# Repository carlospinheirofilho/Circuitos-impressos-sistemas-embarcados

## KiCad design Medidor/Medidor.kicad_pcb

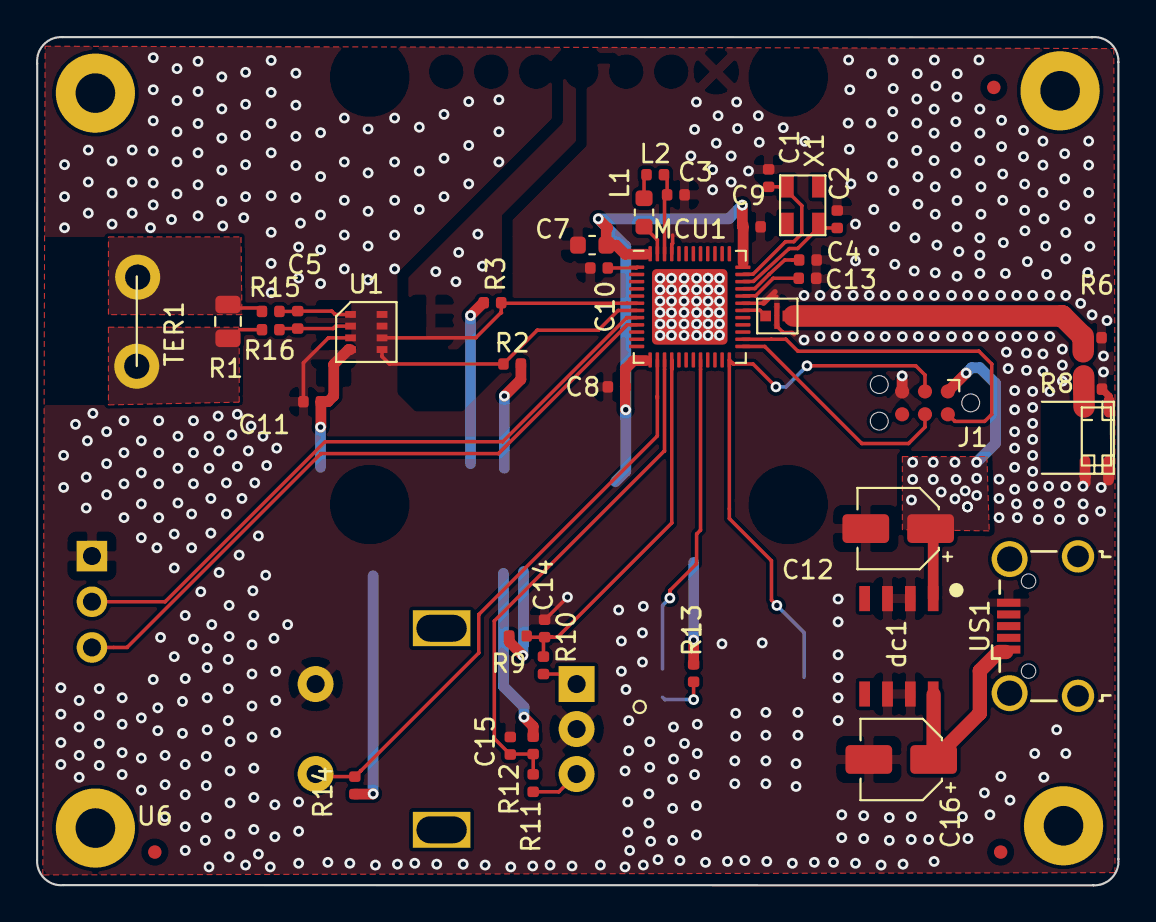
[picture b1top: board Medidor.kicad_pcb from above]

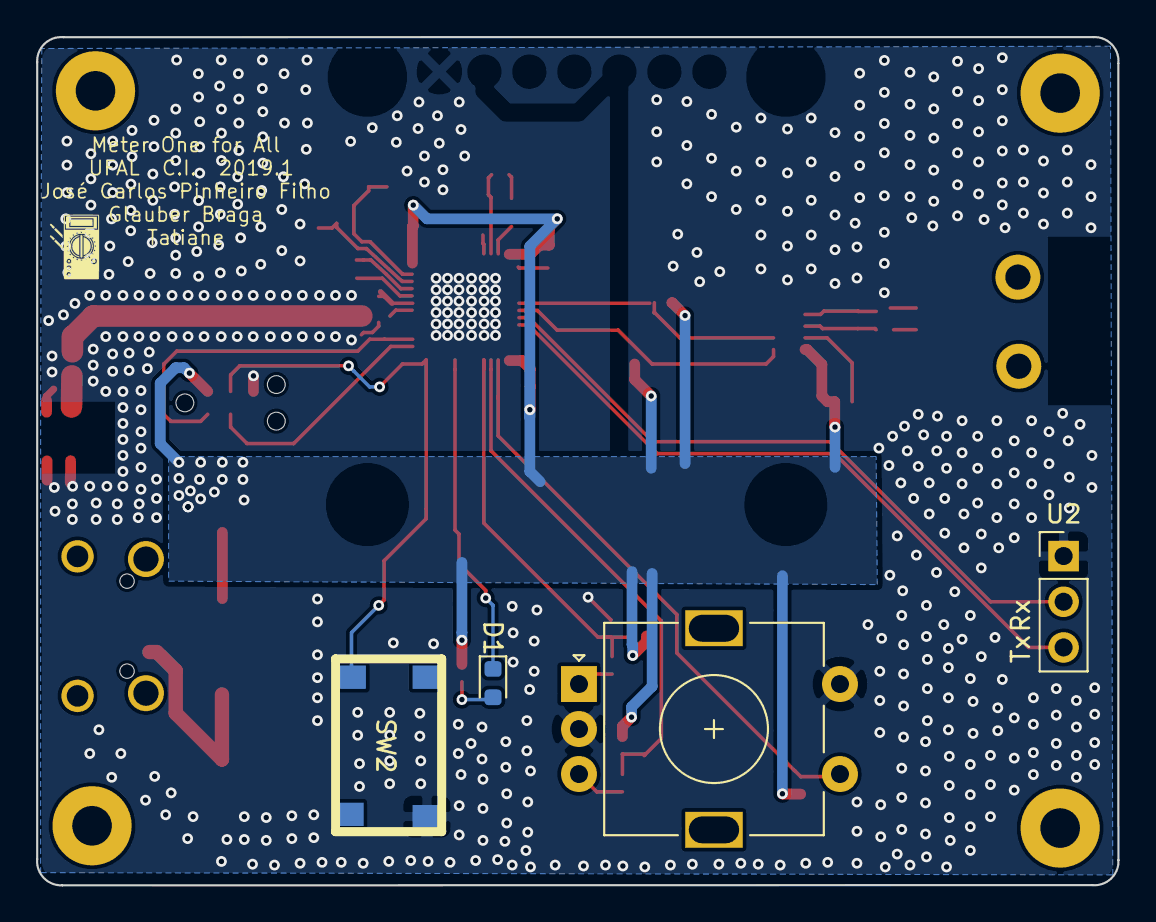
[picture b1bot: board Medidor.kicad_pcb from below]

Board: 2 copper layers, 60.1 x 47.1 mm, 47 parts (4 on the bottom side), 32 nets.

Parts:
C1, C2: 12pF; C_0402_1005Metric
C3: 1uF; C_0402_1005Metric
C4: 100pF; C_0402_1005Metric
C5, C11, C14, C15: 0.1uF; C_0402_1005Metric
C7: 4.7uF; C_0603_1608Metric
C8, C9, C10: 100nF; C_0402_1005Metric
C12: 0.1uF; CP_Elec_4x3
C13: NC; C_0402_1005Metric
C16: 0.33uF; CP_Elec_4x3
D1: LED; LED_0603_1608Metric
Fil1: 2450FM07A0029T; baloon
J1: TC2030-CTX-TAG_CONECT; Tag-Connect_TC2030-IDC-NL_2x03_P1.27mm_Vertical
L1: 10uH; L_0603_1608Metric
L2: 15nH; L_0402_1005Metric
MCU1: nRF52832-QFN4; QFN-48-1EP_6x6mm_P0.4mm_EP4.2x4.2mm
R1: Shunt; R_0805_2012Metric
R2, R3: 1kΩ; R_0402_1005Metric
R6, R8: NC; R_0402_1005Metric
R7: 0; R_0402_1005Metric
R9, R10, R11, R12, R14: 10KΩ; R_0402_1005Metric
R13: 50Ω; R_0402_1005Metric
R15, R16: 10Ω; R_0402_1005Metric
SW1: Rotary_Encoder_Switch; RotaryEncoder_Alps_EC11E-Switch_Vertical_H20mm
SW2: SW_DPST_x2; botao
TER1: terminal-medidor; Screw
U1: INA219-INA; INAright
U2: Serial; PinHeader_1x03_P2.54mm_Vertical
U3: 2450AT18D0100
U4, U5, U6: Fiducial; Fiducial_0.75mm_Mask1.5mm
US1: USB; USB_Micro-B_Wuerth_629105150521_CircularHoles
X1: 32MHz; cristal
dc1: DC-DC; L78L

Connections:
+3V3: C7.2, C8.2, C9.2, C11.2, C12.1, J1.1, MCU1.13, MCU1.36, MCU1.48, R2.2, R3.2, R9.1, R12.1, R13.2, R14.1, U1.4, dc1.1
+5V: C16.1, US1.1, dc1.8
/RF: R7.2, R8.1, U3.1
/RX: MCU1.8, U2.2
/TX: MCU1.9, U2.3
Ant: Fil1.1, MCU1.30
GND: C1.1, C2.1, C3.1, C4.1, C7.1, C8.1, C9.1, C10.1, C11.1, C12.2, C13.2, C14.2, C15.2, C16.2, Fil1.2, Fil1.4, J1.5, MCU1.31, MCU1.45, MCU1.49, R6.2, R8.2, SW1.C, SW1.S2, SW2.2, U1.3, U1.7, U1.8, U2.1, U3.2, U3.3, U3.4, US1.5, dc1.2, dc1.3, dc1.6, dc1.7
LEDMCU: D1.1, MCU1.20
unnamed: C1.2, MCU1.35, X1.1
unnamed: C2.2, MCU1.34, X1.2
unnamed: C3.2, L2.2, MCU1.46
unnamed: C4.2, MCU1.33
unnamed: C5.1, R16.2, U1.2
unnamed: C5.2, R15.2, U1.1
unnamed: C10.2, MCU1.1
unnamed: C13.1, MCU1.32
unnamed: D1.2, R13.1
unnamed: Fil1.3, R6.1, R7.1
unnamed: L1.1, MCU1.47
unnamed: L1.2, L2.1
unnamed: R1.1, R16.1, TER1.2
unnamed: R1.2, R15.1, TER1.1
unnamed: R10.2, SW1.A
unnamed: R11.1, SW1.B
RC1: C14.1, MCU1.16, R9.2, R10.1
RC2: C15.1, MCU1.15, R11.2, R12.2
RC3: MCU1.14, R14.2, SW1.S1
SCL: MCU1.7, R2.1, U1.5
SDA: MCU1.6, R3.1, U1.6
SWDCLK: J1.4, MCU1.25
SWDIO: J1.2, MCU1.26
nRESET: J1.3, MCU1.24, SW2.1

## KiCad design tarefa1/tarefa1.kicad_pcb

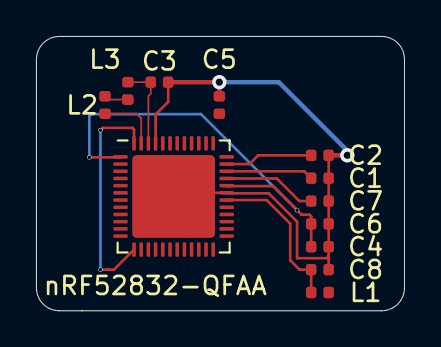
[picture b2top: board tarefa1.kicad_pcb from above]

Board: 2 copper layers, 20.4 x 15.2 mm, 12 parts (0 on the bottom side), 10 nets.

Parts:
C1, C2: 12pF; C_0402_1005Metric
C3, C4, C5, C8: 100nF; C_0402_1005Metric
C6: N.C.; C_0402_1005Metric
C7: 100pF; C_0402_1005Metric
L1, L2: 10microH; L_0402_1005Metric
L3: 10nH; L_0402_1005Metric
nRF52832-QFAA: nRF52832-QFxx; QFN-48-1EP_6x6mm_P0.4mm_EP4.6x4.6mm

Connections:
GND: C1.2, C2.2, C3.2, C4.1, C5.2, C6.2, C7.2, C8.2, nRF52832-QFAA.31, nRF52832-QFAA.45, nRF52832-QFAA.49
unnamed: C1.1, nRF52832-QFAA.34
unnamed: C2.1, nRF52832-QFAA.35
unnamed: C3.1, L3.2, nRF52832-QFAA.46
unnamed: C4.2, C6.1, nRF52832-QFAA.1, nRF52832-QFAA.32
unnamed: C7.1, nRF52832-QFAA.33
unnamed: C8.1, L1.2, nRF52832-QFAA.30
unnamed: L2.1, nRF52832-QFAA.47
unnamed: L2.2, L3.1
VCC: C5.1, nRF52832-QFAA.13, nRF52832-QFAA.36, nRF52832-QFAA.48

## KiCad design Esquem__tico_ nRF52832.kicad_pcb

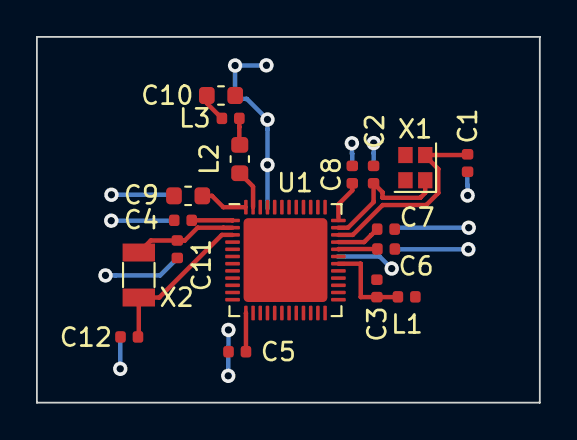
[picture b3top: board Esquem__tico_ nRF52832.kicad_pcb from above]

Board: 2 copper layers, 27.9 x 20.3 mm, 18 parts (0 on the bottom side), 13 nets.

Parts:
C1, C2, C11, C12: 12p; C_0402_1005Metric
C3: 0.8p; C_0402_1005Metric
C4, C5, C8: 100n; C_0402_1005Metric
C6: N.C.; C_0402_1005Metric
C7: 100p; C_0402_1005Metric
C9: 4.7µ; C_0603_1608Metric
C10: 1.0µ; C_0603_1608Metric
L1: 3.9nH; L_0402_1005Metric
L2: 10µ; L_0603_1608Metric
L3: 15n; L_0402_1005Metric
U1: nRF52832; QFN-48-1EP_6x6mm_P0.4mm_EP4.66x4.66mm
X1: 32MHz; Crystal_SMD_2016-4Pin_2.0x1.6mm
X2: 32.768kHz; Crystal_SMD_3215-2Pin_3.2x1.5mm

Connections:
Earth: C1.2, C2.2, C3.2, C4.2, C5.2, C6.2, C7.2, C8.2, C9.2, C10.2, C11.2, C12.2, U1.31, U1.45
unnamed: C1.1, U1.34, X1.2
unnamed: C2.1, U1.35, X1.1
unnamed: C3.1, L1.1, U1.30
unnamed: C4.1, U1.1
unnamed: C6.1, U1.32
unnamed: C7.1, U1.33
unnamed: C10.1, L3.1, U1.46
unnamed: C11.1, U1.2, X2.1
unnamed: C12.1, U1.3, X2.2
unnamed: L2.1, L3.2
unnamed: L2.2, U1.47
VDD: C5.1, C8.1, C9.1, U1.13, U1.36, U1.48

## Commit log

2019-06-05 Tarefa 1
2019-06-12 Adicionando pcb
2019-07-17 Adicionando V1.
    Primeira versão do esquemático.
2019-07-17 Corrigindo DC-DC
2019-07-19 Esquemático mais completo.
2019-07-21 Correção no circuito do encoder
2019-07-21 Add Uart e filtro no ina.
2019-07-22 Add new pdf
2019-07-22 Minor fix
2019-07-24 Add ohm symbol
2019-07-24 Adicionando alguns footprints
2019-07-26 Placement in progress
2019-07-30 Replacement
2019-08-01 more replacement
2019-08-01 conexões
2019-08-01 BOM generated
2019-08-01 Footprints USB, DISPLAY, INA219 E L78L associados
2019-08-01 Ligações feitas
2019-08-02 replacement again and again and again
2019-08-02 bonito
2019-08-03 Acabamento
2019-08-03 acabamento 2
2019-08-03 acabamento 2.1
2019-08-03 Gerando GRBs
2019-09-17 corrigindo.
